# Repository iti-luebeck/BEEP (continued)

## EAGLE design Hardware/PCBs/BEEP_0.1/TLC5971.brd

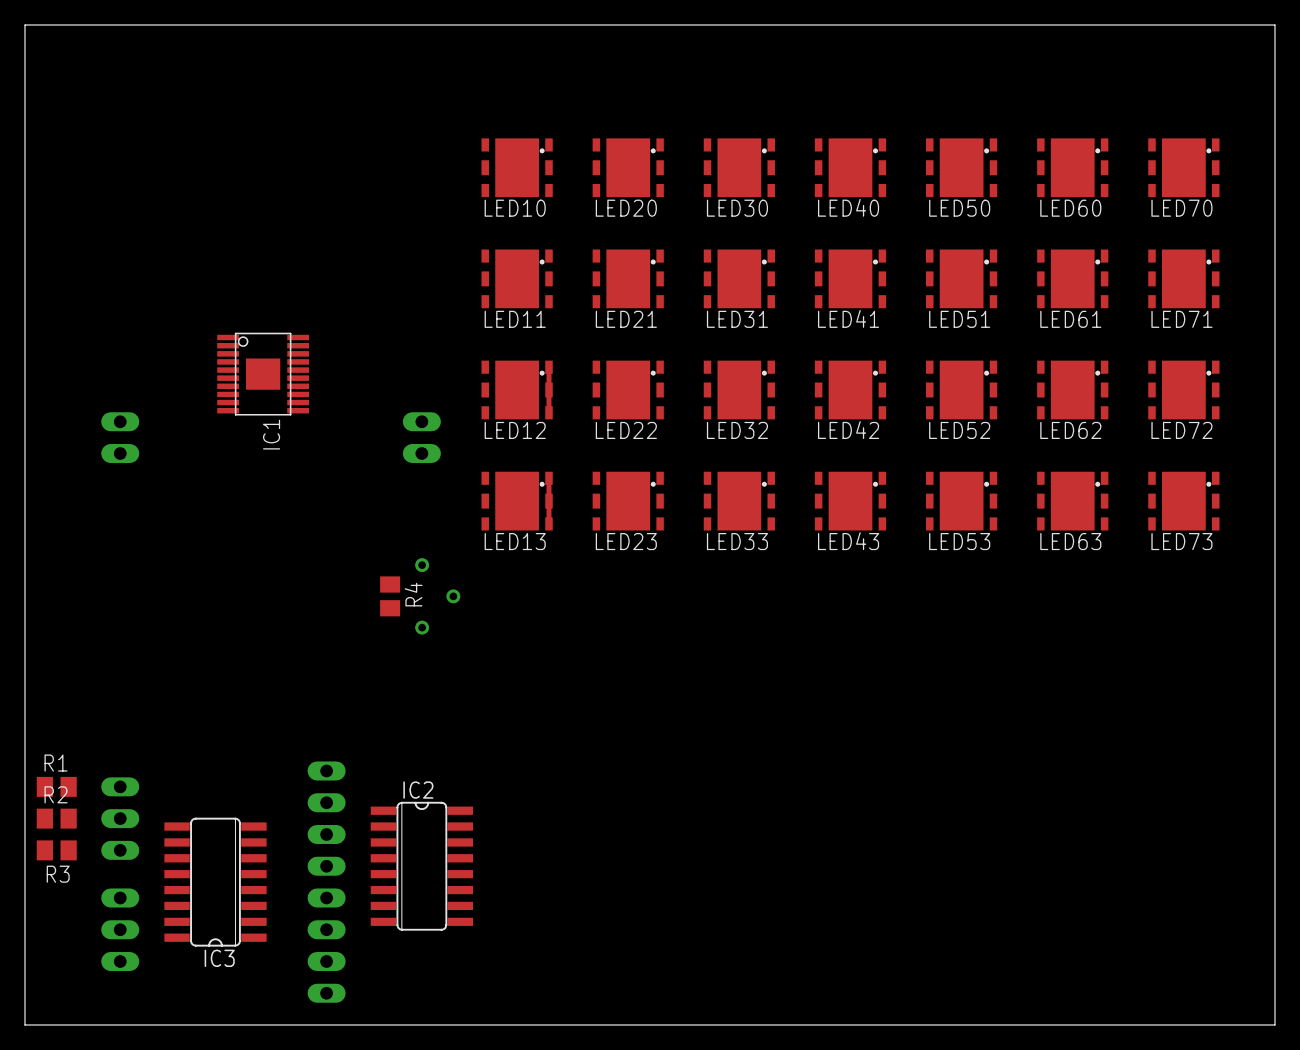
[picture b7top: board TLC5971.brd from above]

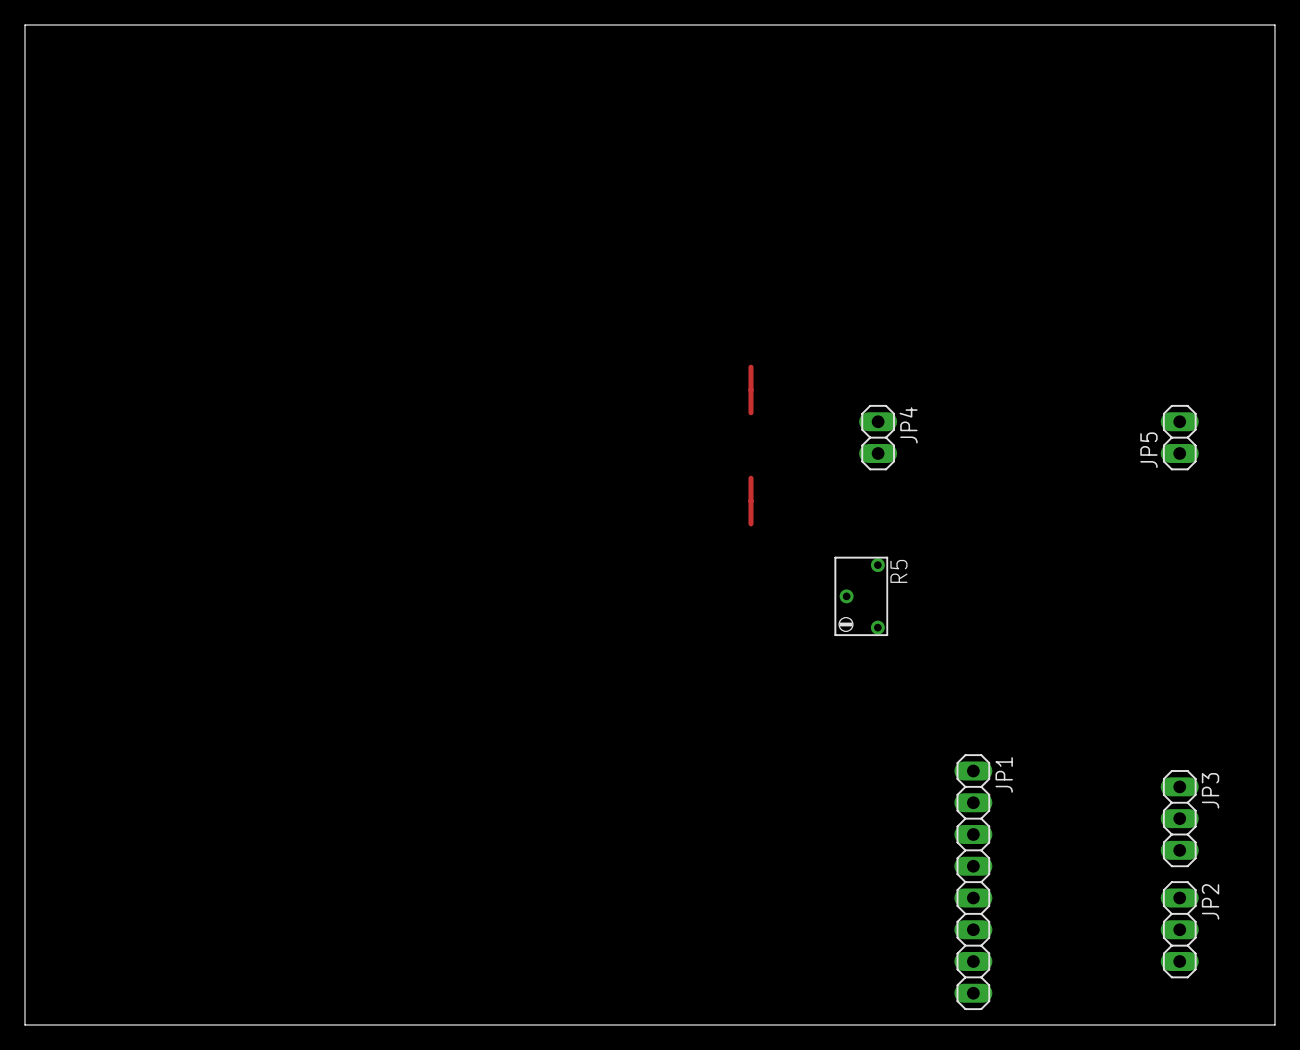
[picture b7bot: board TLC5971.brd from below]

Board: 2 copper layers, 100.0 x 80.0 mm, 41 parts (6 on the bottom side), 40 nets.

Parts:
IC1: TLC5971; HTSSOP-20(PWP)
IC2: ULN2003AD; SO16
IC3: 74AC11238D; SO16
JP1: 1X08
JP2, JP3: 1X03
JP4, JP5: 1X02
LED10, LED11, LED12, LED13, LED20, LED21, LED22, LED23, LED30, LED31, LED32, LED33, LED40, LED41, LED42, LED43, LED50, LED51, LED52, LED53, LED60, LED61, LED62, LED63, LED70, LED71, LED72, LED73: F50360
R1, R2, R3, R4: M0805
R5: RTRIM74W

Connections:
B0: IC1.OUTB0, LED10.BA, LED20.BA, LED30.BA, LED40.BA, LED50.BA, LED60.BA, LED70.BA
B1: IC1.OUTB1, LED11.BA, LED21.BA, LED31.BA, LED41.BA, LED51.BA, LED61.BA, LED71.BA
B2: IC1.OUTB2, LED12.BA, LED22.BA, LED32.BA, LED42.BA, LED52.BA, LED62.BA, LED72.BA
B3: IC1.OUTB3, LED13.BA, LED23.BA, LED33.BA, LED43.BA, LED53.BA, LED63.BA, LED73.BA
G0: IC1.OUTG0, LED10.GA, LED20.GA, LED30.GA, LED40.GA, LED50.GA, LED60.GA, LED70.GA
G1: IC1.OUTG1, LED11.GA, LED21.GA, LED31.GA, LED41.GA, LED51.GA, LED61.GA, LED71.GA
G2: IC1.OUTG2, LED12.GA, LED22.GA, LED32.GA, LED42.GA, LED52.GA, LED62.GA, LED72.GA
G3: IC1.OUTG3, LED13.GA, LED23.GA, LED33.GA, LED43.GA, LED53.GA, LED63.GA, LED73.GA
GND: IC1.GND, IC1.PWP, IC2.8, IC3.4, R1.1, R2.1, R4.1, R5.2
unnamed: IC2.1, IC3.16, JP1.1
unnamed: IC2.2, IC3.1, JP1.2
unnamed: IC2.3, IC3.2, JP1.3
unnamed: IC2.4, IC3.3, JP1.4
unnamed: IC2.5, IC3.5, JP1.5
unnamed: IC2.6, IC3.6, JP1.6
unnamed: IC2.7, IC3.7, JP1.7
unnamed: IC3.8, JP1.8
unnamed: IC3.9, JP3.1, R1.2
unnamed: IC3.10, JP3.2, R2.2
unnamed: IC3.11, JP3.3, R3.1
unnamed: IC3.15, JP2.3
unnamed: IC3.14, JP2.2
unnamed: IC3.13, JP2.1
unnamed: IC2.12, LED50.BC, LED50.GC, LED50.RC, LED51.BC, LED51.GC, LED51.RC, LED52.BC, LED52.GC, LED52.RC, LED53.BC, LED53.GC, LED53.RC
unnamed: IC2.11, LED60.BC, LED60.GC, LED60.RC, LED61.BC, LED61.GC, LED61.RC, LED62.BC, LED62.GC, LED62.RC, LED63.BC, LED63.GC, LED63.RC
unnamed: IC2.10, LED70.BC, LED70.GC, LED70.RC, LED71.BC, LED71.GC, LED71.RC, LED72.BC, LED72.GC, LED72.RC, LED73.BC, LED73.GC, LED73.RC
unnamed: IC2.13, LED40.BC, LED40.GC, LED40.RC, LED41.BC, LED41.GC, LED41.RC, LED42.BC, LED42.GC, LED42.RC, LED43.BC, LED43.GC, LED43.RC
unnamed: IC2.14, LED30.BC, LED30.GC, LED30.RC, LED31.BC, LED31.GC, LED31.RC, LED32.BC, LED32.GC, LED32.RC, LED33.BC, LED33.GC, LED33.RC
unnamed: IC2.15, LED20.BC, LED20.GC, LED20.RC, LED21.BC, LED21.GC, LED21.RC, LED22.BC, LED22.GC, LED22.RC, LED23.BC, LED23.GC, LED23.RC
unnamed: IC2.16, LED10.BC, LED10.GC, LED10.RC, LED11.BC, LED11.GC, LED11.RC, LED12.BC, LED12.GC, LED12.RC, LED13.BC, LED13.GC, LED13.RC
unnamed: IC1.SDTI, JP4.2
unnamed: IC1.SCKI, JP4.1
unnamed: IC1.SCKO, JP5.2
unnamed: IC1.SDTO, JP5.1
unnamed: IC1.IREF, R4.2, R5.3
R0: IC1.OUTR0, LED10.RA, LED20.RA, LED30.RA, LED40.RA, LED50.RA, LED60.RA, LED70.RA
R1: IC1.OUTR1, LED11.RA, LED21.RA, LED31.RA, LED41.RA, LED51.RA, LED61.RA, LED71.RA
R2: IC1.OUTR2, LED12.RA, LED22.RA, LED32.RA, LED42.RA, LED52.RA, LED62.RA, LED72.RA
R3: IC1.OUTR3, LED13.RA, LED23.RA, LED33.RA, LED43.RA, LED53.RA, LED63.RA, LED73.RA
VCC: IC1.VCC, IC1.VREG, IC2.9, IC3.12, R3.2
